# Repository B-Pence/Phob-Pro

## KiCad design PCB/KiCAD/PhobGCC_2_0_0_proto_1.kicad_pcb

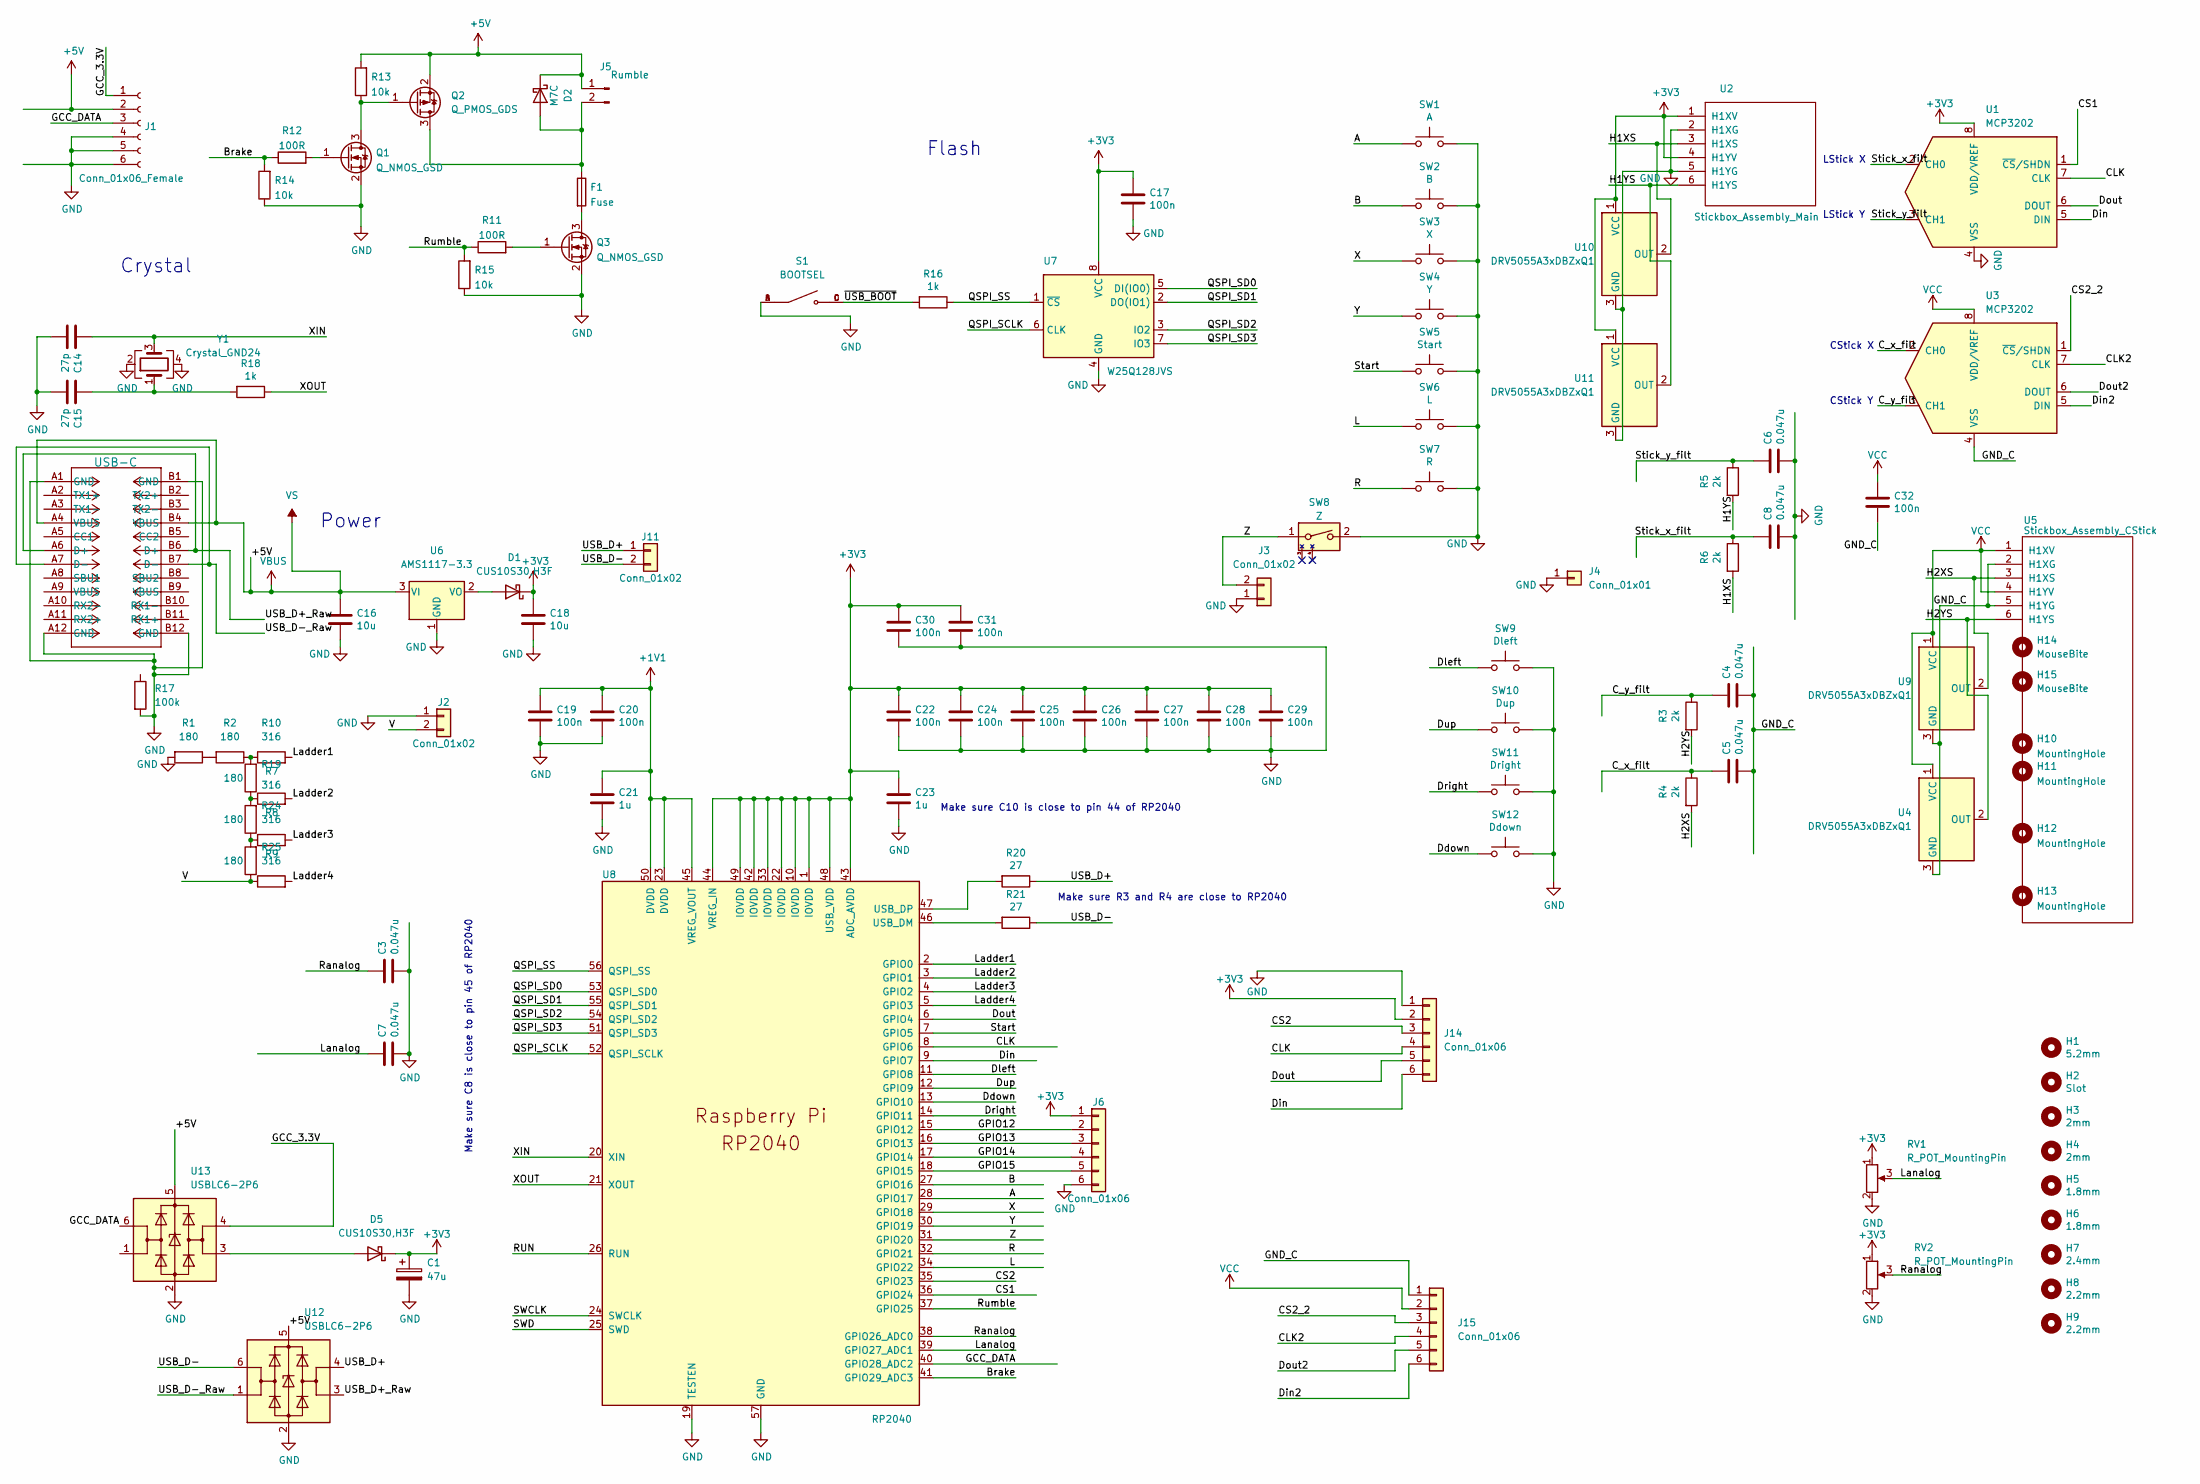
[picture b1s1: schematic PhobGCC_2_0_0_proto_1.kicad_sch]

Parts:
C1: 47u; CP_EIA-3528-12_Kemet-T_Pad1.50x2.35mm_HandSolder; LCSC C136751
C3, C4, C5, C6, C7, C8: 0.047u; C_0603_HandSoldering; LCSC C1622
C14, C15: 27p; C_0402_1005Metric; LCSC C1557
C16, C18: 10u; C_0805_2012Metric; LCSC C15850
C17, C19, C20, C22, C24, C25, C26, C27, C28, C29, C30, C31, C32: 100n; C_0402_1005Metric; LCSC C1525
C21, C23: 1u; C_0402_1005Metric; LCSC C52923
D1, D5: CUS10S30,H3F; D_SOD-323; LCSC C146335
D2: M7C; D_SOD-123; LCSC C8598
F1: Fuse; Fuse_1206_3216Metric; LCSC C69680
H1: 5.2mm; MountingHole_5.2mm
H2: Slot
H3, H4: 2mm; MountingHole_2.0mm
H5, H6: 1.8mm; MountingHole_1.8mm
H7: 2.4mm; MountingHole_2.4mm
H8, H9: 2.2mm; MountingHole_2.2mm
H10: MountingHole; MountingHole_1.8mm
H11: MountingHole; MountingHole_5.2mm
H12, H13: MountingHole; MountingHole_2.0mm
H14: MouseBite; breakaway-mousebites-double-v2-small
H15: MouseBite; breakaway-mousebites-double-v2-large
J1: Conn_01x06_Female; GCC_Header_Straight_1x06_Pitch2.00mm
J2, J11: Conn_01x02; PinHeader_1x02_P2.00mm_Vertical
J3: Conn_01x02; PinHeader_1x02_P2.00mm_Horizontal
J4: Conn_01x01; PinHeader_1x01_P2.54mm_Vertical
J5: Rumble; rumble_pins
J6, J14, J15: Conn_01x06; PinSocket_1x06_P2.00mm_Vertical
J7: USB-C; USB_C_Receptacle_Molex_105450-0101
Q1, Q3: Q_NMOS_GSD; SOT-23; LCSC C20917
Q2: Q_PMOS_GDS; SOT-23; LCSC C15127
R1, R2, R7, R8, R9: 180; R_0402_1005Metric; LCSC C38941
R3, R4, R5, R6: 2k; R_0603_1608Metric_Pad0.98x0.95mm_HandSolder; LCSC C22975
R10, R19, R24, R25: 316; R_0402_1005Metric; LCSC C159037
R11, R12: 100R; R_0603_1608Metric_Pad0.98x0.95mm_HandSolder; LCSC C22775
R13, R14, R15: 10k; R_0603_1608Metric_Pad0.98x0.95mm_HandSolder; LCSC C25804
R16, R18: 1k; C_0402_1005Metric; LCSC C11702
R17: 100k; R_0603_1608Metric_Pad0.98x0.95mm_HandSolder; LCSC C25803
R20, R21: 27; C_0402_1005Metric; LCSC C25100
RV1, RV2: R_POT_MountingPin; GCC_Slider
S1: BOOTSEL; SW_TS-1187A-B-A-B; PARTREV A0
SW1: A; ABXY_Contact_Omron_Switch_Circley
SW2: B; ABXY_Contact_Omron_Switch_Circley
SW3: X; ABXY_Contact_Omron_Switch_Circley
SW4: Y; ABXY_Contact_Omron_Switch_Circley
SW5: Start; Start_Contact
SW6: L; Pin_Header_Straight_1x02_Pitch2.54mm
SW7: R; Pin_Header_Straight_1x02_Pitch2.54mm
SW8: Z; Z_Switch_Edge_Omron
SW9: Dleft; Dpad_Contact_TL3315NF_2
SW10: Dup; Dpad_Contact_TL3315NF_2
SW11: Dright; Dpad_Contact_TL3315NF_2
SW12: Ddown; Dpad_Contact_TL3315NF_2
U1, U3: MCP3202; SOIC-8_3.9x4.9mm_P1.27mm; LCSC C56997
U2: Stickbox_Assembly_Main; GCC_Stickbox_Hall_Only
U4, U9, U10, U11: DRV5055A3xDBZxQ1; SOT-23; LCSC C266128
U5: Stickbox_Assembly_CStick; GCC_Stickbox_Hall_Only
U6: AMS1117-3.3; SOT-223-3_TabPin2; LCSC C6186
U7: W25Q128JVS; SOIC-8_5.23x5.23mm_P1.27mm; LCSC C97521
U8: RP2040; RP2040-QFN-56; LCSC C2040
U12, U13: USBLC6-2P6; SOT-666; LCSC C2827693
Y1: Crystal_GND24; Crystal_SMD_3225-4Pin_3.2x2.5mm; LCSC C40395

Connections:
+1V1: C19.1, C20.1, C21.1, U8.23 (DVDD), U8.45 (VREG_VOUT), U8.50 (DVDD)
+3V3: C1.1, C17.1, C18.1, C22.1, C23.1, C24.1, C25.1, C26.1, C27.1, C28.1, C29.1, C30.1, C31.1, D1.1 (K), D5.1 (K), J6.1, J14.2, RV1.1 (V+), RV2.1 (V+), U1.8 (VDD/VREF), U2.1 (H1XV), U2.4 (H1YV), U7.8 (VCC), U8.1 (IOVDD), U8.10 (IOVDD), U8.22 (IOVDD), U8.33 (IOVDD), U8.42 (IOVDD), U8.43 (ADC_AVDD), U8.44 (VREG_IN), U8.48 (USB_VDD), U8.49 (IOVDD), U10.1 (VCC), U11.1 (VCC)
+5V: C16.1, D2.1 (K), J1.2, J5.1, J7.A4 (VBUS), J7.B4 (VBUS), Q2.2 (S), R13.2, U6.3 (VI), U12.5 (VBUS), U13.5 (VBUS)
/A: SW1.1, U8.28 (GPIO17)
/B: SW2.1, U8.27 (GPIO16)
/Brake: R12.1, R14.2, U8.41 (GPIO29_ADC3)
/CLK: J14.4, U1.7 (CLK), U8.8 (GPIO6)
/CLK2: J15.4, U3.7 (CLK)
/CS1: U1.1 (~CS/SHDN), U8.36 (GPIO24)
/CS2: J14.3, U8.35 (GPIO23)
/CS2_2: J15.3, U3.1 (~CS/SHDN)
/C_x_filt: C5.1, R4.1, U3.2 (CH0)
/C_y_filt: C4.1, R3.1, U3.3 (CH1)
/Ddown: SW12.1, U8.13 (GPIO10)
/Din: J14.6, U1.5 (DIN), U8.9 (GPIO7)
/Din2: J15.6, U3.5 (DIN)
/Dleft: SW9.1, U8.11 (GPIO8)
/Dout: J14.5, U1.6 (DOUT), U8.6 (GPIO4)
/Dout2: J15.5, U3.6 (DOUT)
/Dright: SW11.1, U8.14 (GPIO11)
/Dup: SW10.1, U8.12 (GPIO9)
/GCC_3.3V: J1.1, U13.4 (I/O2)
/GCC_DATA: J1.3, U8.40 (GPIO28_ADC2), U13.6 (I/O1)
/GND_C: C4.2, C5.2, C32.2, J15.1, U3.4 (VSS), U4.3 (GND), U5.2 (H1XG), U5.5 (H1YG), U9.3 (GND)
/GPIO12: J6.2, U8.15 (GPIO12)
/GPIO13: J6.3, U8.16 (GPIO13)
/GPIO14: J6.4, U8.17 (GPIO14)
/GPIO15: J6.5, U8.18 (GPIO15)
/H1XS: R6.2, U2.3 (H1XS), U10.2 (OUT)
/H1YS: R5.2, U2.6 (H1YS), U11.2 (OUT)
/H2XS: R4.2, U5.3 (H1XS), U9.2 (OUT)
/H2YS: R3.2, U4.2 (OUT), U5.6 (H1YS)
/L: SW6.1, U8.34 (GPIO22)
/Ladder1: R10.2, U8.2 (GPIO0)
/Ladder2: R19.2, U8.3 (GPIO1)
/Ladder3: R24.2, U8.4 (GPIO2)
/Ladder4: R25.2, U8.5 (GPIO3)
/Lanalog: C7.1, RV1.3 (Signal), U8.39 (GPIO27_ADC1)
/QSPI_SCLK: U7.6 (CLK), U8.52 (QSPI_SCLK)
/QSPI_SD0: U7.5 (DI(IO0)), U8.53 (QSPI_SD0)
/QSPI_SD1: U7.2 (DO(IO1)), U8.55 (QSPI_SD1)
/QSPI_SD2: U7.3 (IO2), U8.54 (QSPI_SD2)
/QSPI_SD3: U7.7 (IO3), U8.51 (QSPI_SD3)
/QSPI_SS: R16.1, U7.1 (~CS), U8.56 (QSPI_SS)
/R: SW7.1, U8.32 (GPIO21)
/RUN: U8.26 (RUN)
/Ranalog: C3.1, RV2.3 (Signal), U8.38 (GPIO26_ADC0)
/Rumble: R11.1, R15.2, U8.37 (GPIO25)
/SWCLK: U8.24 (SWCLK)
/SWD: U8.25 (SWD)
/Start: SW5.1, U8.7 (GPIO5)
/Stick_x_filt: C8.1, R6.1, U1.2 (CH0)
/Stick_y_filt: C6.1, R5.1, U1.3 (CH1)
/USB_D+: J11.1, R20.1, U12.4 (I/O2)
/USB_D+_Raw: J7.A6 (D+), J7.B6 (D+), U12.3 (I/O2)
/USB_D-: J11.2, R21.1, U12.6 (I/O1)
/USB_D-_Raw: J7.A7 (D-), J7.B7 (D-), U12.1 (I/O1)
/V: J2.2, R9.1, R25.1
/X: SW3.1, U8.29 (GPIO18)
/XIN: C14.1, U8.20 (XIN), Y1.3
/XOUT: R18.1, U8.21 (XOUT)
/Y: SW4.1, U8.30 (GPIO19)
/Z: J3.2, SW8.1, U8.31 (GPIO20)
/~USB_BOOT: R16.2, S1.C, S1.D
GND: C1.2, C3.2, C6.2, C7.2, C8.2, C14.2, C15.2, C16.2, C17.2, C18.2, C19.2, C20.2, C21.2, C22.2, C23.2, C24.2, C25.2, C26.2, C27.2, C28.2, C29.2, C30.2, C31.2, J1.4, J1.5, J1.6, J2.1, J3.1, J4.1, J6.6, J7.A1 (GND), J7.A12 (GND), J7.B1 (GND), J7.B12 (GND), J14.1, Q1.2 (S), Q3.2 (S), R1.2, R14.1, R15.1, R17.2, RV1.2 (GND), RV2.2 (GND), S1.A, S1.B, SW1.2, SW2.2, SW3.2, SW4.2, SW5.2, SW6.2, SW7.2, SW8.2, SW9.2, SW10.2, SW11.2, SW12.2, U1.4 (VSS), U2.2 (H1XG), U2.5 (H1YG), U6.1 (GND), U7.4 (GND), U8.19 (TESTEN), U8.57 (GND), U10.3 (GND), U11.3 (GND), U12.2 (GND), U13.2 (GND), Y1.2, Y1.4
unnamed: C15.1, R18.2, Y1.1
unnamed: D1.2 (A), U6.2 (VO)
unnamed: D2.2 (A), F1.1, J5.2, Q2.3 (D)
unnamed: D5.2 (A), U13.3 (I/O2)
unnamed: Q1.3 (D), Q2.1 (G), R13.1
unnamed: Q1.1 (G), R12.2
unnamed: F1.2, Q3.3 (D)
unnamed: Q3.1 (G), R11.2
unnamed: R1.1, R2.2
unnamed: R2.1, R7.2, R10.1
unnamed: R7.1, R8.2, R19.1
unnamed: R8.1, R9.2, R24.1
unnamed: R21.2, U8.46 (USB_DM)
unnamed: R20.2, U8.47 (USB_DP)
VCC: C32.1, J15.2, U3.8 (VDD/VREF), U4.1 (VCC), U5.1 (H1XV), U5.4 (H1YV), U9.1 (VCC)

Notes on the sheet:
Power
LStick Y
Make sure C10 is close to pin 44 of RP2040
CStick Y
Make sure R3 and R4 are close to RP2040
Make sure C8 is close to pin 45 of RP2040
Flash
Crystal
CStick X
LStick X

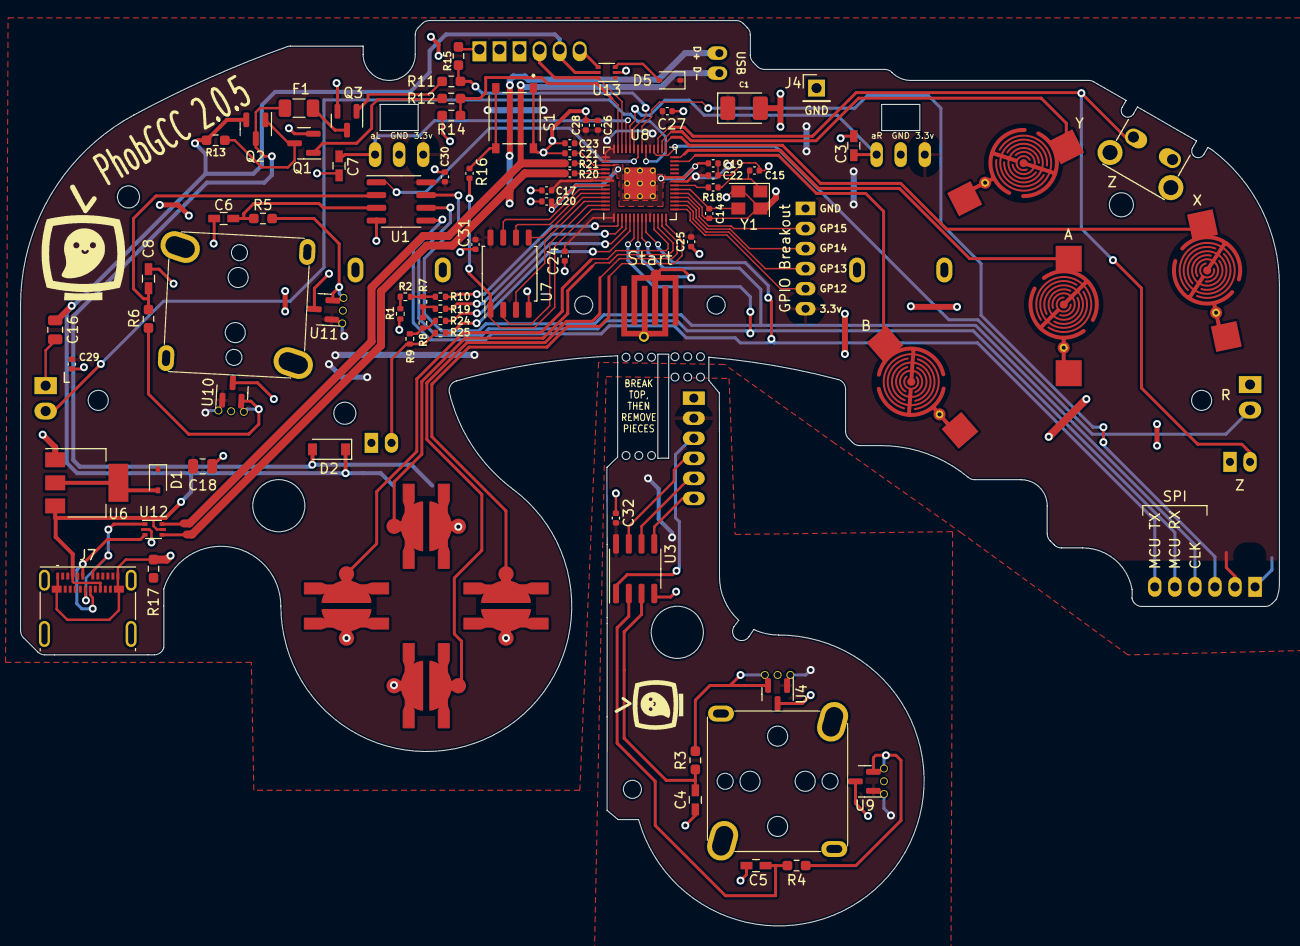
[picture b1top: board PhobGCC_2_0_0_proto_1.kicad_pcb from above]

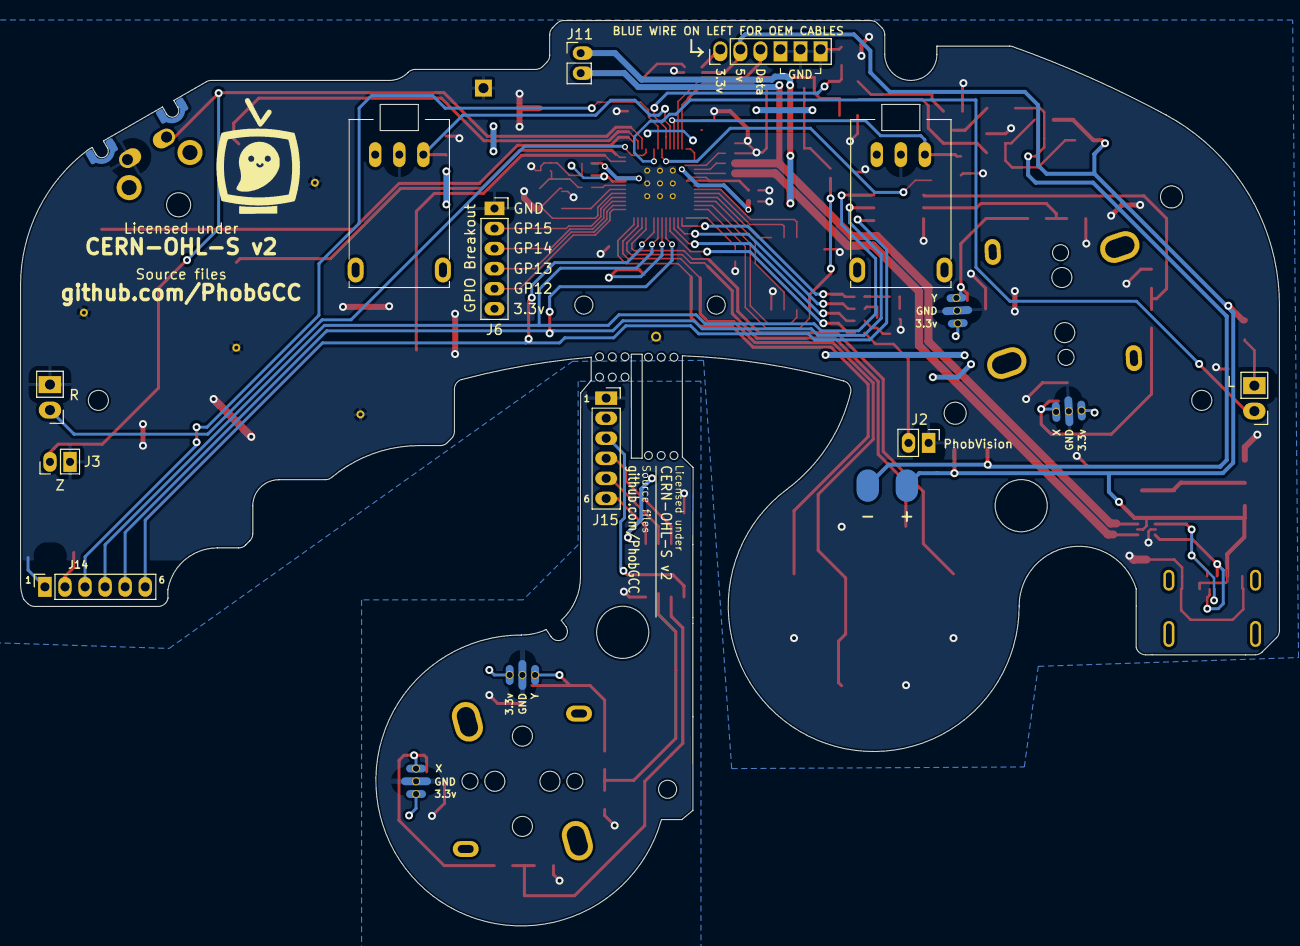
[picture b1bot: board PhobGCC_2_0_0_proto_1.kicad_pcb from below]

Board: 2 copper layers, 125.5 x 90.3 mm, 113 parts (13 on the bottom side), 77 nets.

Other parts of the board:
Gphobtvbigback: LOGO; phobtv_bold_big
Gphobtvbigback#2: LOGO; phobtv_bold_big
Gtvsmallfrontc: LOGO; phobtv_bold_smol

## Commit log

2024-05-08 Implemented USB-C For Flashing
2024-05-16 Updated .gitignore

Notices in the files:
PCB/KiCAD/PhobGCC_2_0_0_proto_1.kicad_pcb:
CERN-OHL-S v2
Licensed under
